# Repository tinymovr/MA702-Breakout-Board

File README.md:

# MA702-Breakout Board

Simple example of using the [MA702 breakout board](https://tinymovr.com/collections/all/products/ma702-breakout) with Arduino.

The project can be directly opened and built using PlatformIO.
Monitor baud rate is 115200.

Board schematic and layout files are in [hardware/](./hardware)

An example usable with the Arduino IDE is in [Arduino/](./Arduino)

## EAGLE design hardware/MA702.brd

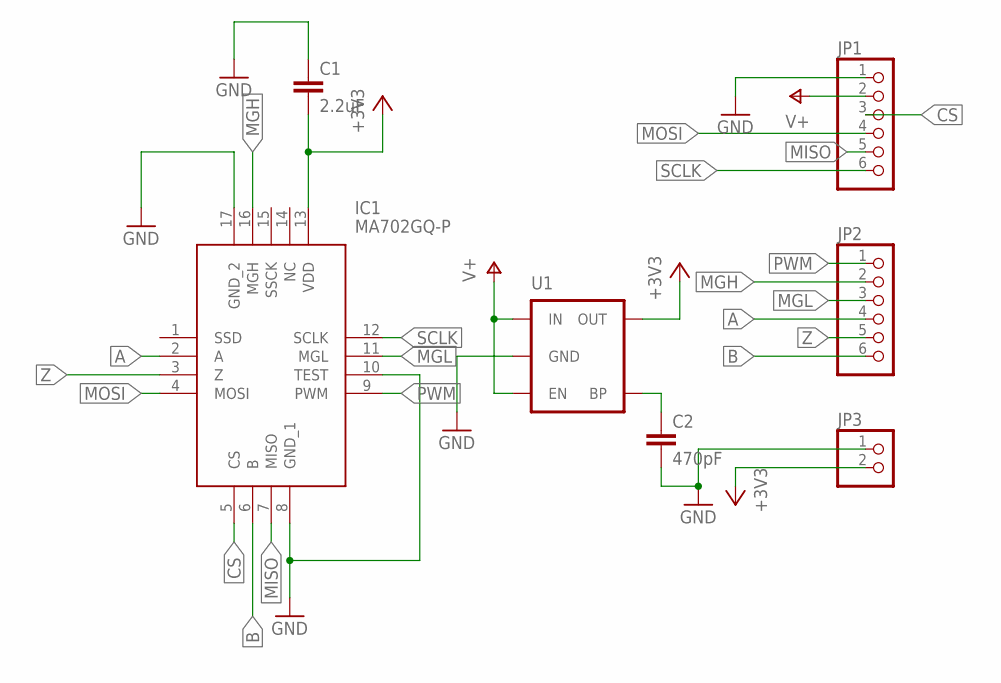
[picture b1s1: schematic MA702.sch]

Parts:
C1: 2.2uF; C0603
C2: 470pF; C0603
IC1: MA702GQ-P; QFN50P300X300X100-17N
JP1, JP2: PINHD-1X06_2.54-S; 1X06-S
JP3: PINHD-1X02_2.54-S; 1X02-S
U1: SPARKFUN-POWERIC_MIC52053.3V; SPARKFUN-POWERIC_SOT23-5

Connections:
+3V3: C1.2, IC1.13 (VDD), JP3.2, U1.5 (OUT)
A: IC1.2 (A), JP2.4
B: IC1.6 (B), JP2.6
CS: IC1.5 (CS), JP1.3
GND: C1.1, C2.2, IC1.8 (GND_1), IC1.10 (TEST), IC1.17 (GND_2), JP1.1, JP3.1, U1.2 (GND)
MGH: IC1.16 (MGH), JP2.2
MGL: IC1.11 (MGL), JP2.3
MISO: IC1.7 (MISO), JP1.5
MOSI: IC1.4 (MOSI), JP1.4
unnamed: C2.1, U1.4 (BP)
PWM: IC1.9 (PWM), JP2.1
SCLK: IC1.12 (SCLK), JP1.6
V+: JP1.2, U1.1 (IN), U1.3 (EN)
Z: IC1.3 (Z), JP2.5

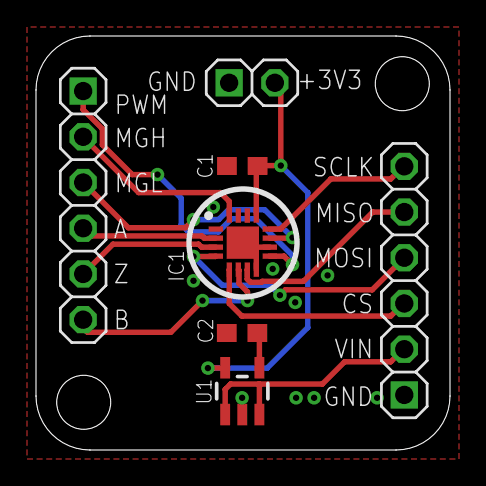
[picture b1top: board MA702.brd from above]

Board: 2 copper layers, 23.0 x 23.0 mm, 7 parts (0 on the bottom side), 14 nets.

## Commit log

2020-10-25 Create LICENSE
2020-10-25 add schematics
2021-04-11 Reduce SPI rate
2024-04-03 update board revision
2024-04-03 add hw license
2024-04-03 update license
2024-04-03 add gitignore
2024-04-03 add Arduino code
2024-06-06 ignore files

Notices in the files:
hardware/MA702.brd:
MA702 (c)2020
